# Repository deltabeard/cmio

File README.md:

# cmio

**Note that this circuit is currently untested, as such I cannot guarantee that
it will function correctly.**

This is a custom Raspberry Pi Compute Module IO Board. Designed for low cost
production, and a minimal set of components.

Because low cost production was the main focus of the project, this Compute
Module IO board only has a subset of features in comparison to the official
version. However, whilst the official version costs £115, this design aims to
produce a Compute Module IO board that can be manufactured (PCB fabrication,
BOM, et al) under £30.

See BOM.md for the bill of materials, and for the costs required to manufacture
the latest release of this board.

This allows hobbyists an opportunity to introduce themselves to the Raspberry
Pi Compute Module without breaking the bank.

Features:
* Low cost design.
* Only low cost components required.
* Simple to solder with a heat gun.
* Micro SD card slot.
* Composite video output (No HDMI).
* Bank 0 and Bank 1 GPIO pins available.
* USB On-The-Go (OTG) support.
* Micro USB power input.
* Fully open source (KiCad files, etc. all available) under TAPR Open Hardware
  License.
* ~~A most excellent reset button!~~ [Removed in v0.5](https://github.com/deltabeard/cmio/commit/58f6f0d9b9edc8a3ccf51f042ef9ee13f27d9331)

Compatibility with the Raspberry Pi GPIO header was removed after v0.2 to
simplify the design and reduce cost of production.

\* Prices correct at the time of writing, are in Pound Sterling and include
VAT.

## Using this Repository

Note that only tagged releases should be used for manufacture (see the
[releases](https://github.com/deltabeard/cmio/releases) page). Other commits
should be deemed as work in progress.

Releases marked as "Pre-release" are not fully tested, and should not be used.
To this date, *no release version is fully working unfortunately*.

## Roadmap

Version v1.0 will denote a fully working board.

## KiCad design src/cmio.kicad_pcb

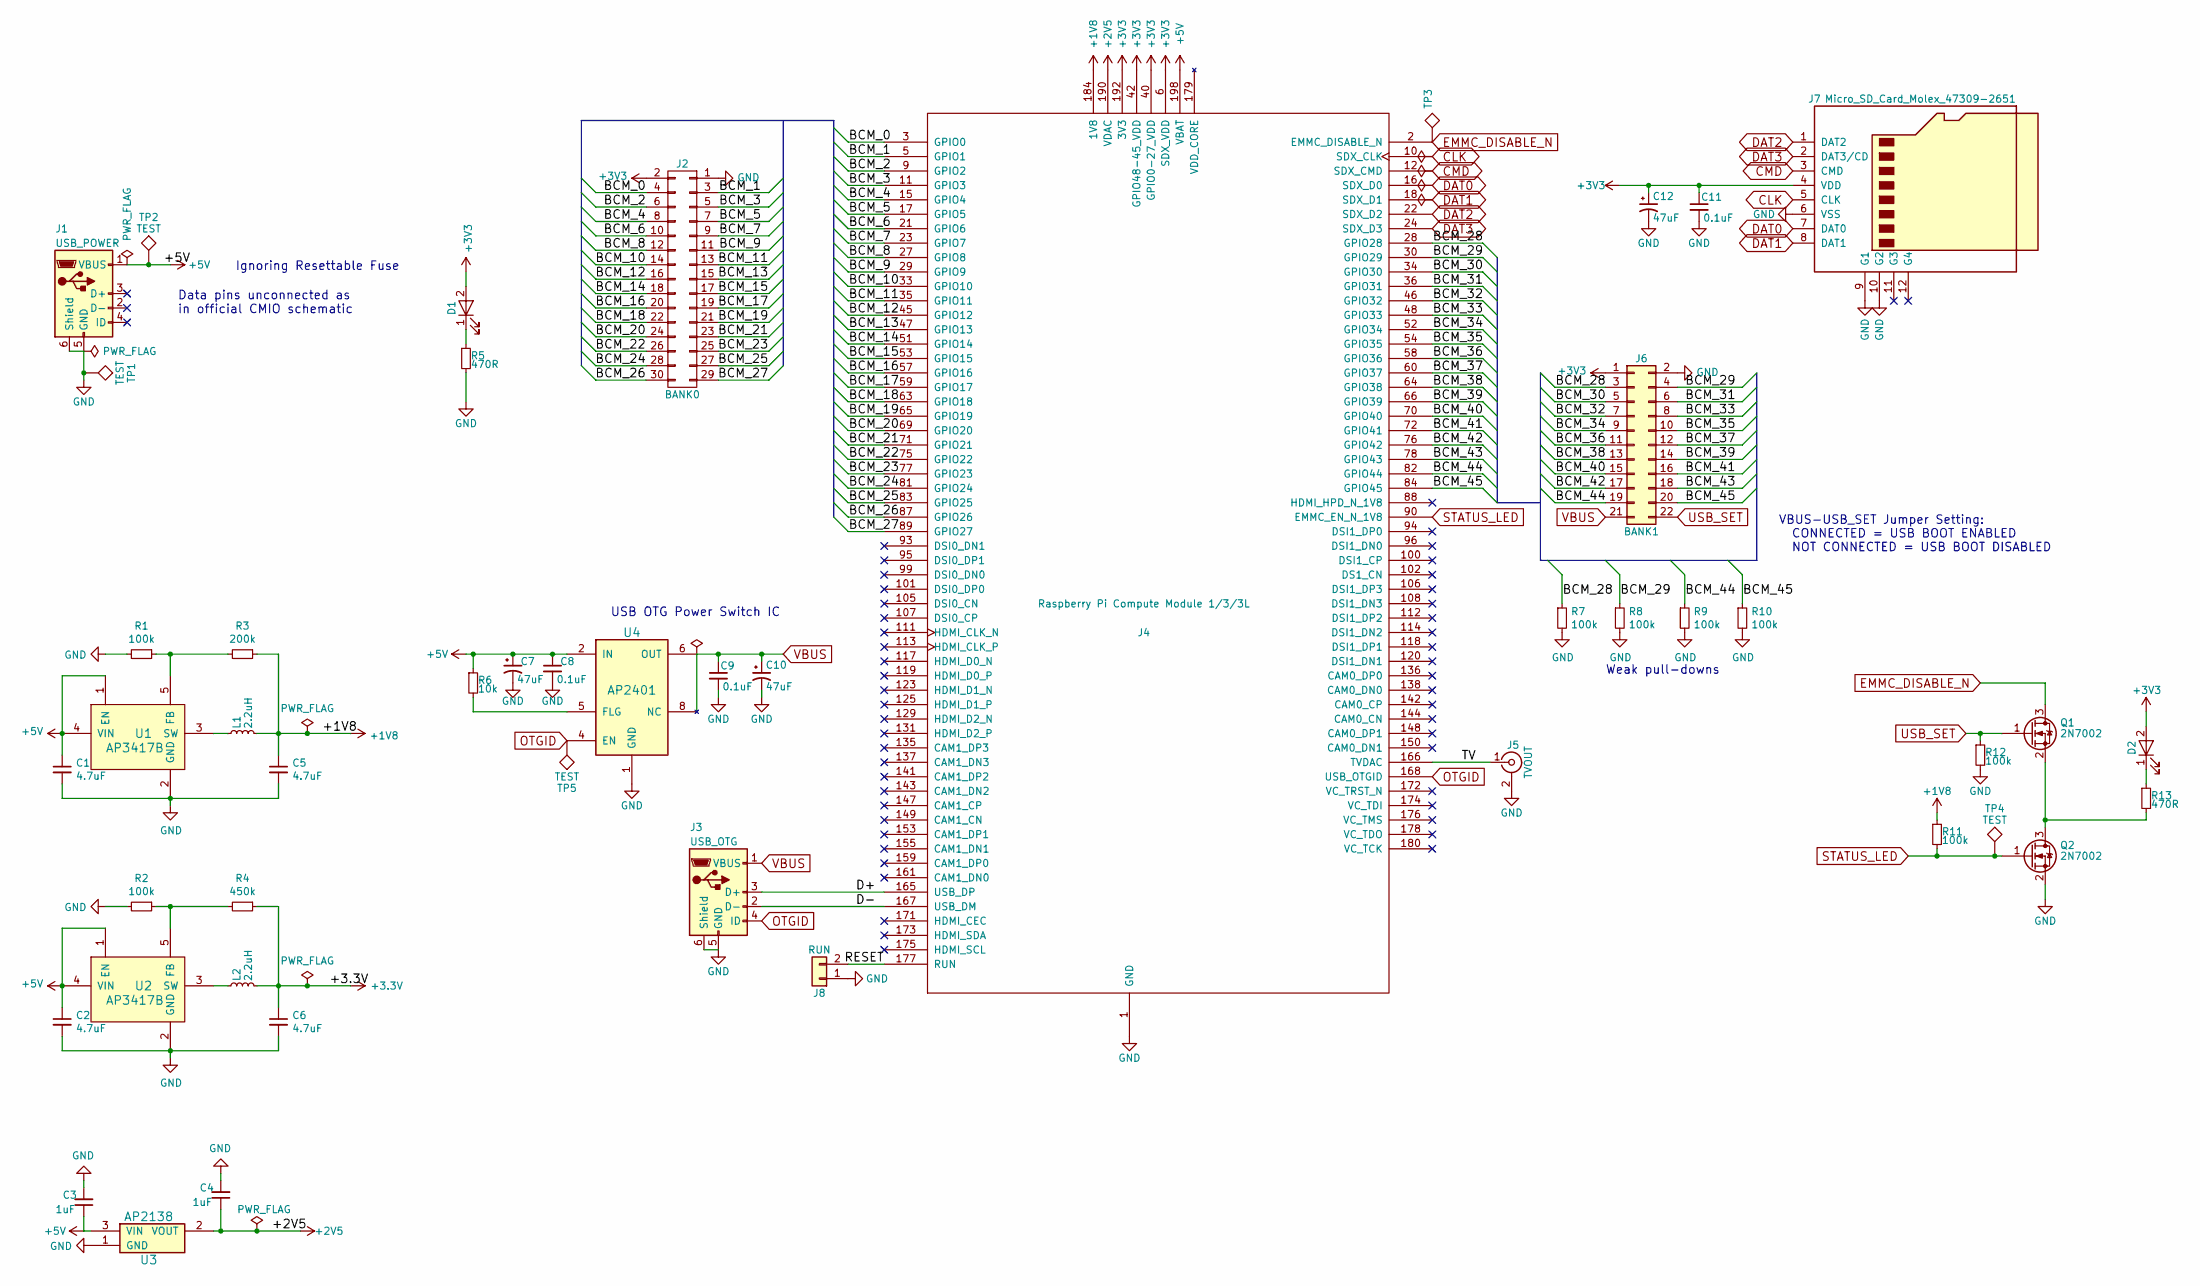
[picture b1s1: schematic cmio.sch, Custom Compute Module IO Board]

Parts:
C1, C2, C5, C6: 4.7uF; C_0805_HandSoldering
C3, C4: 1uF; C_0805_HandSoldering
C7, C10, C12: 47uF; CP_Tantalum_Case-A_EIA-3216-18_Reflow
C8, C9: 0.1uF; C_0805_HandSoldering
C11: 0.1uF; C_0805
D1: PWR LED; LED_0805
D2: STATUS LED; LED_0805
J1: USB_POWER; Molex_Right_Angle_SMT_TypeB_MicroUSB_105017_CircularOnly_an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
J2: BANK0; Pin_Header_Straight_2x15_Pitch2.54mm
J3: USB_OTG; Molex_Right_Angle_SMT_TypeB_MicroUSB_105017_CircularOnly_an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
J4: Raspberry Pi Compute Module 1/3/3L; CM3_Socket_SODIMM_DDR1-2_TE_1473149_4_NoHole_NoEndSilkS
J5: TVOUT; RCA_PHONO
J6: BANK1; Pin_Header_Straight_2x11_Pitch2.54mm_SMD
J7: Micro_SD_Card_Molex_47309-2651; Molex_Micro_SD_47309-2651
J8: RUN; Pin_Header_Straight_1x02_Pitch2.54mm
L1, L2: 2.2uH; Neosid_Inductor_SM-NE29_SMD1008
Q1, Q2: 2N7002; SOT-23
R1, R2, R7, R8, R9, R10, R11, R12: 100k; R_0805_HandSoldering
R3: 200k; R_0805_HandSoldering
R4: 450k; R_0805_HandSoldering
R5, R13: 470R; R_0805_HandSoldering
R6: 10k; R_0805_HandSoldering
TP1, TP2, TP3, TP4, TP5: TEST; Measurement_Point_Round-SMD-Pad_Small
U1, U2: AP3417B; SOT-23-5_HandSoldering
U3: AP2138; SOT-23
U4: AP2401; MSOP-8_3x3mm_Pitch0.65mm

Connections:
+1V8: C5.1, J4.183 (1V8), J4.184 (1V8), J4.185 (1V8), J4.186 (1V8), L1.2, R3.1, R11.1
+2V5: C4.1, J4.189 (VDAC), J4.190 (VDAC), U3.2 (VOUT)
+5V: C1.1, C2.1, C3.1, C7.1, C8.1, J1.1 (VBUS), J4.197 (VBAT), J4.198 (VBAT), J4.199 (VBAT), J4.200 (VBAT), R6.1, TP2.1, U1.1 (EN), U1.4 (VIN), U2.1 (EN), U2.4 (VIN), U3.3 (VIN), U4.2 (IN), U4.3 (IN)
/BCM_0: J2.4, J4.3 (GPIO0)
/BCM_1: J2.3, J4.5 (GPIO1)
/BCM_2: J2.6, J4.9 (GPIO2)
/BCM_3: J2.5, J4.11 (GPIO3)
/BCM_4: J2.8, J4.15 (GPIO4)
/BCM_5: J2.7, J4.17 (GPIO5)
/BCM_6: J2.10, J4.21 (GPIO6)
/BCM_7: J2.9, J4.23 (GPIO7)
/BCM_8: J2.12, J4.27 (GPIO8)
/BCM_9: J2.11, J4.29 (GPIO9)
/BCM_10: J2.14, J4.33 (GPIO10)
/BCM_11: J2.13, J4.35 (GPIO11)
/BCM_12: J2.16, J4.45 (GPIO12)
/BCM_13: J2.15, J4.47 (GPIO13)
/BCM_14: J2.18, J4.51 (GPIO14)
/BCM_15: J2.17, J4.53 (GPIO15)
/BCM_16: J2.20, J4.57 (GPIO16)
/BCM_17: J2.19, J4.59 (GPIO17)
/BCM_18: J2.22, J4.63 (GPIO18)
/BCM_19: J2.21, J4.65 (GPIO19)
/BCM_20: J2.24, J4.69 (GPIO20)
/BCM_21: J2.23, J4.71 (GPIO21)
/BCM_22: J2.26, J4.75 (GPIO22)
/BCM_23: J2.25, J4.77 (GPIO23)
/BCM_24: J2.28, J4.81 (GPIO24)
/BCM_25: J2.27, J4.83 (GPIO25)
/BCM_26: J2.30, J4.87 (GPIO26)
/BCM_27: J2.29, J4.89 (GPIO27)
/BCM_28: J4.28 (GPIO28), J6.3, R7.1
/BCM_29: J4.30 (GPIO29), J6.4, R8.1
/BCM_30: J4.34 (GPIO30), J6.5
/BCM_31: J4.36 (GPIO31), J6.6
/BCM_32: J4.46 (GPIO32), J6.7
/BCM_33: J4.48 (GPIO33), J6.8
/BCM_34: J4.52 (GPIO34), J6.9
/BCM_35: J4.54 (GPIO35), J6.10
/BCM_36: J4.58 (GPIO36), J6.11
/BCM_37: J4.60 (GPIO37), J6.12
/BCM_38: J4.64 (GPIO38), J6.13
/BCM_39: J4.66 (GPIO39), J6.14
/BCM_40: J4.70 (GPIO40), J6.15
/BCM_41: J4.72 (GPIO41), J6.16
/BCM_42: J4.76 (GPIO42), J6.17
/BCM_43: J4.78 (GPIO43), J6.18
/BCM_44: J4.82 (GPIO44), J6.19, R9.1
/BCM_45: J4.84 (GPIO45), J6.20, R10.1
/D+: J3.3 (D+), J4.165 (USB_DP)
/D-: J3.2 (D-), J4.167 (USB_DM)
/RESET: J4.177 (RUN), J8.2
/TV: J4.166 (TVDAC), J5.1 (In)
CLK: J4.10 (SDX_CLK), J7.5 (CLK)
CMD: J4.12 (SDX_CMD), J7.3 (CMD)
DAT0: J4.16 (SDX_D0), J7.7 (DAT0)
DAT1: J4.18 (SDX_D1), J7.8 (DAT1)
DAT2: J4.22 (SDX_D2), J7.1 (DAT2)
DAT3: J4.24 (SDX_D3), J7.2 (DAT3/CD)
EMMC_DISABLE_N: J4.2 (EMMC_DISABLE_N), Q1.3 (D), TP3.1
GND: C1.2, C2.2, C3.2, C4.2, C5.2, C6.2, C7.2, C8.2, C9.2, C10.2, C11.2, C12.2, J1.5 (GND), J1.6 (Shield), J2.1, J3.5 (GND), J3.6 (Shield), J4.1 (GND), J4.7 (GND), J4.8 (GND), J4.13 (GND), J4.14 (GND), J4.19 (GND), J4.20 (GND), J4.25 (GND), J4.26 (GND), J4.31 (GND), J4.32 (GND), J4.37 (GND), J4.38 (GND), J4.43 (GND), J4.44 (GND), J4.49 (GND), J4.50 (GND), J4.55 (GND), J4.56 (GND), J4.61 (GND), J4.62 (GND), J4.67 (GND), J4.68 (GND), J4.73 (GND), J4.74 (GND), J4.79 (GND), J4.80 (GND), J4.85 (GND), J4.86 (GND), J4.91 (GND), J4.92 (GND), J4.97 (GND), J4.98 (GND), J4.103 (GND), J4.104 (GND), J4.109 (GND), J4.110 (GND), J4.115 (GND), J4.116 (GND), J4.121 (GND), J4.122 (GND), J4.127 (GND), J4.133 (GND), J4.134 (GND), J4.139 (GND), J4.140 (GND), J4.145 (GND), J4.146 (GND), J4.151 (GND), J4.152 (GND), J4.157 (GND), J4.163 (GND), J4.164 (GND), J4.169 (GND), J4.170 (GND), J4.181 (GND), J4.182 (GND), J4.187 (GND), J4.188 (GND), J4.195 (GND), J4.196 (GND), J5.2 (Ext), J6.2, J7.6 (VSS), J7.9 (G1), J7.10 (G2), J8.1, Q2.2 (S), R1.2, R2.2, R5.2, R7.2, R8.2, R9.2, R10.2, R12.2, TP1.1, U1.2 (GND), U2.2 (GND), U3.1 (GND), U4.1 (GND)
unnamed: D1.1 (K), R5.1
unnamed: D2.1 (K), R13.1
unnamed: L1.1, U1.3 (SW)
unnamed: L2.1, U2.3 (SW)
unnamed: Q1.2 (S), Q2.3 (D), R13.2
unnamed: R1.1, R3.2, U1.5 (FB)
unnamed: R2.1, R4.2, U2.5 (FB)
unnamed: R6.2, U4.5 (FLG)
OTGID: J3.4 (ID), J4.168 (USB_OTGID), TP5.1, U4.4 (EN)
STATUS_LED: J4.90 (EMMC_EN_N_1V8), Q2.1 (G), R11.2, TP4.1
USB_SET: J6.22, Q1.1 (G), R12.1
VBUS: C9.1, C10.1, J3.1 (VBUS), J6.21, U4.6 (OUT), U4.7 (OUT), U4.8 (NC)

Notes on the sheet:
Weak pull-downs
Ignoring Resettable Fuse
Data pins unconnected as in official CMIO schematic
USB OTG Power Switch IC
VBUS-USB_SET Jumper Setting: CONNECTED = USB BOOT ENABLED NOT CONNECTED = USB BOOT DISABLED

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
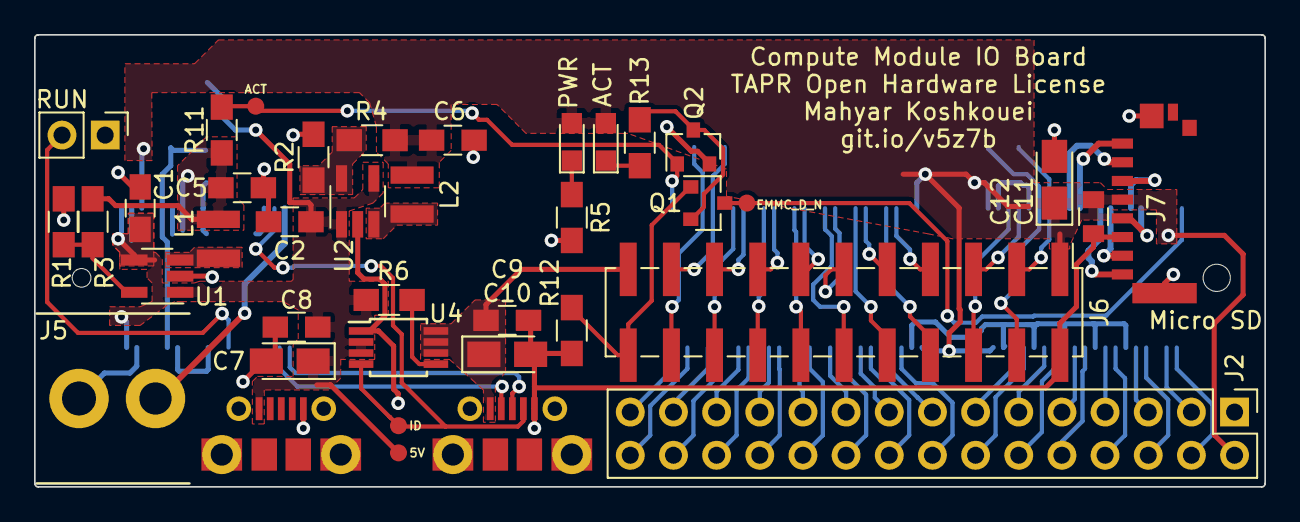
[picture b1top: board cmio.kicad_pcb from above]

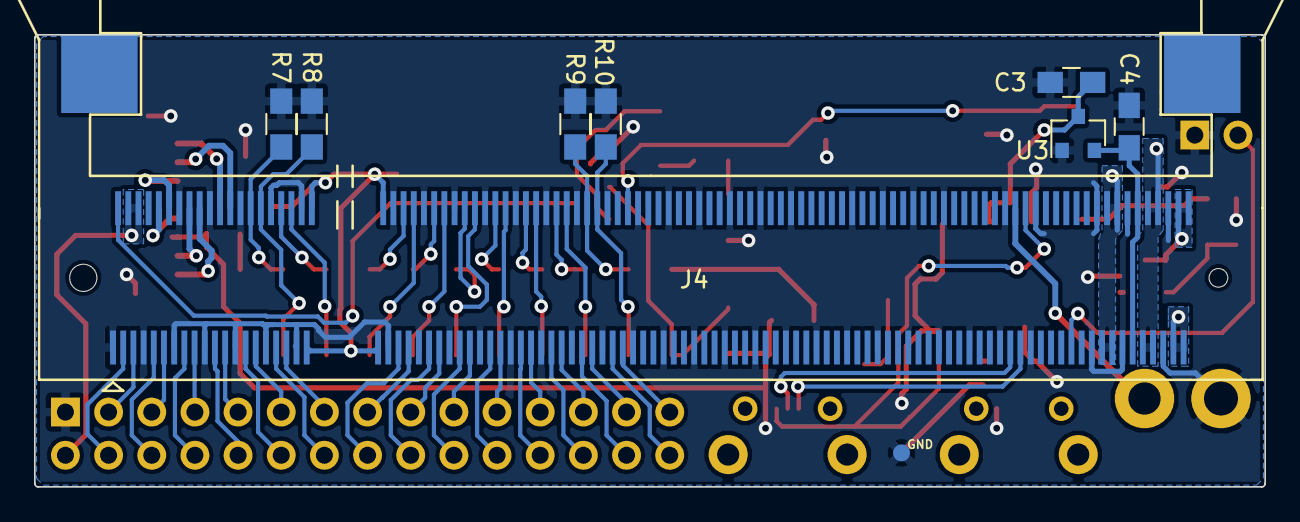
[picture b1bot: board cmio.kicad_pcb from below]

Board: 2 copper layers, 72.4 x 26.6 mm, 48 parts (9 on the bottom side), 74 nets.

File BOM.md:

# Bill of materials for version 0.4

Items marked as a *Generic* manufacturer can typically be replaced with other components of the same value, size, etc.

Remember to perform your own research in to what component is best for you; there may be more cost effective components by the time you are reading this.

| Id | Designator | Quantity | Value | Notes | Supplier | Supplier Product Number | Manufacturer | Manufacturer Part Number | Datasheet URL | Cost Each | Cost Total | Cost (Per Pack) |
|----|------------|----------|-------|-------|----------|-------------------------|--------------|--------------------------|---------------|-----------|------------|-----------------|
| 1 | J8 | 1 | Micro_SD_Card_TFP09_2_12B | SD Card Slot | Aliexpress | [32637089909](https://www.aliexpress.com/item/10Pcs-TransFlash-TF-Micro-Me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 | Centenary Materials | 104554/TFP09-2-12B | [URL](http://images.100y.com.tw/pdf_file/10-TFP09-2-12B.pdf)/[URL]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 | 0.055 | 0.055 | £0.55 |
| 2 | J7 | 1 | BANK1 | 2.54mm Pitch, SMD, 20-Pin | RS | [673-7339](http://uk.rs-online.com/web/p/pcb-headers/6737339/) | Generic | 95278-101-16LF | [URL](http://docs-europe.electrocomponents.com/webdocs/0d78/090076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 | 0.542 | 0.542 | £2.71 |
| 3 | C1,C2,C3,C4,C6,C7 | 6 | 4.7uF | Ceramic Cap, >6V, 0805 | RS | [698-3579](http://uk.rs-online.com/web/p/ceramic-multilayer-capacitors/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 | Generic | 0805ZD475KAT2A | [URL](http://docs-europe.electrocomponents.com/webdocs/0def/090076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 | 0.027 | 0.162 | £0.27 |
| 4 | C5 | 1 | 10nF | Ceramic Cap, >6V, 0805 | RS | [264-4371](http://uk.rs-online.com/web/p/ceramic-multilayer-capacitors/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 | Generic | C0805C103K5RACTU | [URL](http://docs-europe.electrocomponents.com/webdocs/1528/090076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 | 0.019 | 0.019 | £0.48 |
| 5 | C8,C9,C11 | 3 | 0.1uF | Ceramic Cap, >6V, 0805 | RS | [264-4416](http://uk.rs-online.com/web/p/ceramic-multilayer-capacitors/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 | Generic | C0805C104K5RACTU | [URL](http://docs-europe.electrocomponents.com/webdocs/1528/090076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 | 0.027 | 0.081 | £0.68 |
| 6 | L1,L2 | 2 | 2.2uH | Inductor, >500mA, 1008 | RS | [786-7112](http://uk.rs-online.com/web/p/multilayer-surface-mount-induc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 | Generic | LQM2HPN2R2MG0L | [URL](http://docs-europe.electrocomponents.com/webdocs/1256/090076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 | 0.2 | 0.4 | £2.00 |
| 7 | R1,R2,R6,R7,R8,R9 | 6 | 100k | Resistor, 0805 | RS | [223-0691](http://uk.rs-online.com/web/p/surface-mount-fixed-resistors/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 | Generic | CRG0805F100K | [URL](http://docs-europe.electrocomponents.com/webdocs/13d0/090076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 | 0.005 | 0.03 | £0.25 |
| 8 | R3 | 1 | 200k | Resistor, 0805 | RS | [832-6735](http://uk.rs-online.com/web/p/surface-mount-fixed-resistors/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 | Generic | CRCW0805200KJNEA | [URL](http://docs-europe.electrocomponents.com/webdocs/13a4/090076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 | 0.027 | 0.027 | £0.27 |
| 9 | R4 | 1 | 450k | Resistor, 0805 | RS | [708-6925](http://uk.rs-online.com/web/p/surface-mount-fixed-resistors/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 | Generic | ERA6AEB4533V | [URL](http://docs-europe.electrocomponents.com/webdocs/0eb1/090076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 | 0.042 | 0.042 | £0.21 |
| 10 | R5 | 1 | 10k | Resistor, 0805 | RS | [832-6723](http://uk.rs-online.com/web/p/surface-mount-fixed-resistors/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 | Generic | CRCW080510K0JNEA | [URL](http://docs-europe.electrocomponents.com/webdocs/13a4/090076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 | 0.028 | 0.028 | £0.28 |
| 11 | SW1 | 1 | Reset | Tactile Push Button | Aliexpress | [32435561950](https://www.aliexpress.com/item/100-pcs-4-4-1-5mm-Tactile-Pu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 | Generic | - | - | 0.0113 | 0.0113 | £1.13 |
| 12 | U1,U2 | 2 | AP3417B | Buck, Adj, 1.2A, SOT-23, 5-Pin | RS | <font face="Liberation Serif">[828-7463](http://uk.rs-online.com/web/p/dc-dc-converters/8287463/)</font> | DiodesZetex | AP3417BK-ADJTRG1 | [URL](http://docs-europe.electrocomponents.com/webdocs/1332/090076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 | 0.099 | 0.198 | £2.48 |
| 13 | U3 | 1 | SP6203EM5-L-2-8/TR | LDO, 2.8V, 300mA, SOT-23, 5-Pin | RS | [686-5761](http://uk.rs-online.com/web/p/low-dropout-voltage-regulators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 | EXAR | SP6203EM5-L-2-8/TR | [URL](http://docs-europe.electrocomponents.com/webdocs/0d9e/090076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 | 0.194 | 0.194 | £1.94 |
| 14 | U4 | 1 | AP2401 | USB Power Switch, Active Low, MSOP, 8-Pin | RS | [822-8830](http://uk.rs-online.com/web/p/usb-power-switches/8228830/) | DiodesZetex | AP2401MP-13 | [URL](http://docs-europe.electrocomponents.com/webdocs/1321/090076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 | 0.081 | 0.081 | £2.03 |
| 15 | J3 | 1 | BANK0 | 2.54mm Pitch, Through hole, 30-Pin | RS | - | Generic | - | - | 0 | 0 | £0.00 |
| 16 | C10,C12 | 2 | 47uF | Tantalum Cap, >6V, 3216-18 | RS | [699-2860](http://uk.rs-online.com/web/p/tantalum-capacitors/6992860/) | AVX | TAJA476K006R | [URL](http://docs-europe.electrocomponents.com/webdocs/0df8/090076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 | 0.091 | 0.182 | £0.91 |
| 17 | J6 | 1 | TVOUT | Video Connector | Aliexpress | [32792221853](https://www.aliexpress.com/item/10PCS-LOT-AV-8-4-5-2x-Holes-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 | Generic | - | [URL](https://ae01.alicdn.com/kf/HTB101RLPFXXXXaMaXXXq6xXFXXXA/123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 | 0.099 | 0.099 | £0.99 |
| 18 | J5 | 1 | CM3Lite | DDR2 DIMM Socket | RS | [719-8725](http://uk.rs-online.com/web/p/dimm-sockets/7198725/) | TE Connectivity | 1473149-4 | [URL](http://docs-europe.electrocomponents.com/webdocs/0f83/090076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 | 1.85 | 1.85 | £1.85 |
| 19 | J4 | 2 | USB_OTG/USB_POWER | USB Micro Socket | RS | [848-6764](http://uk.rs-online.com/web/p/micro-usb-connectors/8486764/) | Molex | 105017-0001 | [URL](http://docs-europe.electrocomponents.com/webdocs/1388/090076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 | 0.356 | 0.712 | £1.78 |
| 20 | N/A | 1 | PCB Fabrication | Ordered with OSH Park | OSH Park | - | - | - | [URL](https://oshpark.com/) | 4.54667 | 4.54667 | £13.64 |


## Total

The total cost for the required quantity is **£9.26** without tax.

Because most of the items had to be purchased in bulk, the total cost is actually **£34.43** without tax.

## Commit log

2017-05-24 Add Computer Module 3 Lite
2017-05-25 Add LDO for 2.8V and 1.8V
2017-05-26 Add Micro SD Card Footprint and 20-TQFP
2017-05-27 Before removing RPi GPIO Compat
2017-05-27 Nearly finished routing
    Remember to remove redundant GND tracks
2017-05-28 Final Checks
2017-06-05 Many changes
    Added pull downs to the four GPIO pins that do not have a pull down or
    pull up integrated.
    Using surface mount pin sockets to reduce PCB space.
    Using copper fills for some power tracks.
    Using thicker tracks for power.
    Added decoupling capacitor close to SD card.
2017-06-05 Update Readme
    Add preview image.
2017-06-19 Minor changes that I can't remember
2017-06-19 Many Changes
    * Add voltage test points. Fixes #10.
    * Repositioned components.
    * Removed some jumpers.
    * Added clearer silkscreen for Reset and TV output. Fixes #8.
    * Fixed Micro USB footprints. Fixes #4.
2017-06-22 Finish routing
    Additionally, added micro USB socket without holes.
2017-06-24 Cleanup and new release
2017-09-02 Some changes to old design
2017-09-03 Complete Redesign
    - Fixed the net name of OTGID.
    - Fixed USB OTG power switch.
    - Added more decoupling capacitors.
    - Connected VBAT directly to 5V.
    - Changed Buck-Boost converter to Buck converter with reduced output
    current.
2017-09-03 Fix footprint tags
2017-09-07 Finish PCB Routing
2017-09-07 Fix Readme
2017-09-10 Simplify CM3 Module Part
    Additionally removed some unnecessary decoupling capacitors.
    Additionally changes the pin allocations on GPIO Bank 1 to optimise
    track length.
    Additionally added PWR_FLAG to fix some ERC errors.
2017-09-10 Improve CM3 Footprint
    Additionally removed electrolytic capacitors.
    Re-annotated components and cleared board.
2017-09-10 Add Heatsink Footprint
    It's cheap, large, and will most likely work well with the heat output
    of the Compute Module 3.
2017-09-17 Add USB and Heatsink footprints
2017-09-17 Replaced ICs
    Using buck converters with simpler design requirements and lower cost.
    Using an LDO for VDAC due to lower noise and low current requirements.
2017-09-17 Add associations
2017-09-17 Some work on PCB
2017-09-17 Remove compatibility with RPi for simpler design
2017-09-20 Complete routing
2017-09-20 Add Board info to Silk Screen
2017-09-20 Replace graphic renders
    Web optimised.
2017-09-21 Add GND VIAs
2017-09-22 Add test points
2017-09-22 Change Micro USB footprint with circular pads only
    For support with OSH Park.
2017-09-25 Change license to TAPR Open Hardware License
2017-09-25 Update preview image to reflect license change
2017-09-26 Use little k for resistor values
2017-09-26 Add message to see BOM.md in README
2017-09-26 Add BOM source spreadsheet
2017-09-26 Update bottom 3D image
2017-11-10 Fixed RAM slot footprint
    Fixed an issue whereby the two large pads where not the right size or in
    the right place.
2017-11-10 Fix annular ring of USB footprint
2017-11-11 Add more footprints
2017-11-11 Major Changes
    - Add USB Boot setting
    - Add Status and Power LEDs
    - Added a second Micro SD slot with a different footprint to allow users
    more variety. They cannot be used at the same time.
    - Use 2.5V for Video DAC, as used in the official CMIO board.
    - Add test points.
2017-11-11 Add notes regarding releases
2017-11-11 Minor changes
    These are minor changes that missed previous commits as I forgot to
    save.
2017-11-12 Fix DRC issues
    Additionally added repository URL to title block.
2017-11-13 Complete Placement
2017-11-20 Finish routing
2017-11-20 Update images
2017-11-20 Minor change to README.me
2017-11-20 Change to IO board
2017-12-01 Add cap and minor changes
    Added an extra decoupling capacitor to the SD socket.
    Replaced the RUN button with an unpopulated two pin header as seen on
    the Raspberry Pi. I can't imagine RUN being used often enough to warrant
    a button.
    Only use one Micro SD socket footprint.
2017-12-02 Increase size of 3V3 plane

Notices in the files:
src/cmio.kicad_pcb:
Licensed under the TAPR Open Hardware License (www.tapr.org/OHL)
